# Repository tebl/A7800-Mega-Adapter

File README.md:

# Atari 7800 Mega Adapter
Let's face it, the controllers that came with the Atari 7800 are truly painful to use... unfortunately, both of the variants for the system suffer from the same problem (just for different reasons)! This may go a long way to explain why I've spent somewhere around an hour total playing on the system despite owning it for a few years, so I thought it was about time I did something about it. The easiest option is to just use a single-button joystick, but then I'd lose out on the features the second button provides so I decided to just use a different controller instead; the Sega Mega Drive / Genesis controller.

I based this project on the FAQ over at AtariAge.com, so if the design looks like something you've seen before then that's probably the reason why. I've built it up and tested it on my Atari 7800 PAL system, seems to work pretty good with the wired 3-button controller (don't have a 6-button variant to test out with). Unfortunately it doesn't seem to work with the new wireless 8bitdo controllers, but at least I finally get to test out some of the games without my hands aching and turning intolerable after 5-minutes of game time.

If you want an alternative to using a Sega Mega Drive controller, I've also created an [adapter](https://github.com/tebl/C64-JoyKEY/tree/main/adapters/Atari%207800) so that my [C64 JoyKEY](https://github.com/tebl/C64-JoyKEY)-controller can be used with the Atari 7800 system.

## Building the adapter
Mark Fixes Stuff on Youtube did a segment called [Making a Sega Megadrive Controller Adapter for Atari 7800! Full Build & Games Testing!](https://www.youtube.com/watch?v=7EVtcfSCWJM) that shows every part of assembling this adapter, particularly useful for those of us that are not used to soldering together new equipment from a bucket of parts. Keep reading from at more text-oriented description of the assembly process.

One thing to note, the main PCB of the Atari 7800 isn't actually mounted flat so the controller ports are actually angled quite a bit downwards! This means that the female DSUB-9 port that goes into the Atari 7800 will have to be soldered in place at an agle, preferably as far as you can take it and still be able to solder the pins into place.

As can also be seen in the picture above, the metal shroud that comes mounted on the female DSUB-9 has been removed after soldering it into place. The male connectors on the Atari 7800 console is made out of plastic and not metal, so it no longer serves a purpose - the plastic on these have also grown brittle over the years, so reducing the strain on it will hopefully also keep it from splitting).

# Schematic
The supplied KiCad files should be sufficient as both a schematic and as a  starting point for ordering PCBs (basically you could just zip the contents of the export folder and upload that on a fabrication site), the schematic is also available in [PDF-format](https://github.com/tebl/A7800-Mega-Adapter/blob/master/export/A7800%20Mega%20Adapter.pdf) and this is what you'll need to print and work your way through this things don't work as expected after assembly.

# BOM
Most parts should be easy to get a hold of from your favourite local electronic component shop, but given that I don't have access to such shops where I live so everything was based on whatever I could get cheapest from eBay/AliExpress (free shipping, plan on waiting 3-4 weeks for delivery though).

| Reference    | Item                                  | Count | Order |
| ------------ | ------------------------------------- | ----- | ----- |
| PCB          | Fabricate using Gerber files          |     1 | [PCBway](https://www.pcbway.com/project/shareproject/Atari_7800_Mega_Drive_adapter.html) |
| J1           | Female DB9 right-angle connector      |     1 |       |
| J2           | Male DB9 right-angle connector        |     1 |       |
| Q1,Q2        | 2N3906 TO-92 transistor               |     2 |       |
| R1,R3        | 620 ohm resistor                      |     2 |       |
| R2,R4        | 1k ohm resistor                       |     2 |       |

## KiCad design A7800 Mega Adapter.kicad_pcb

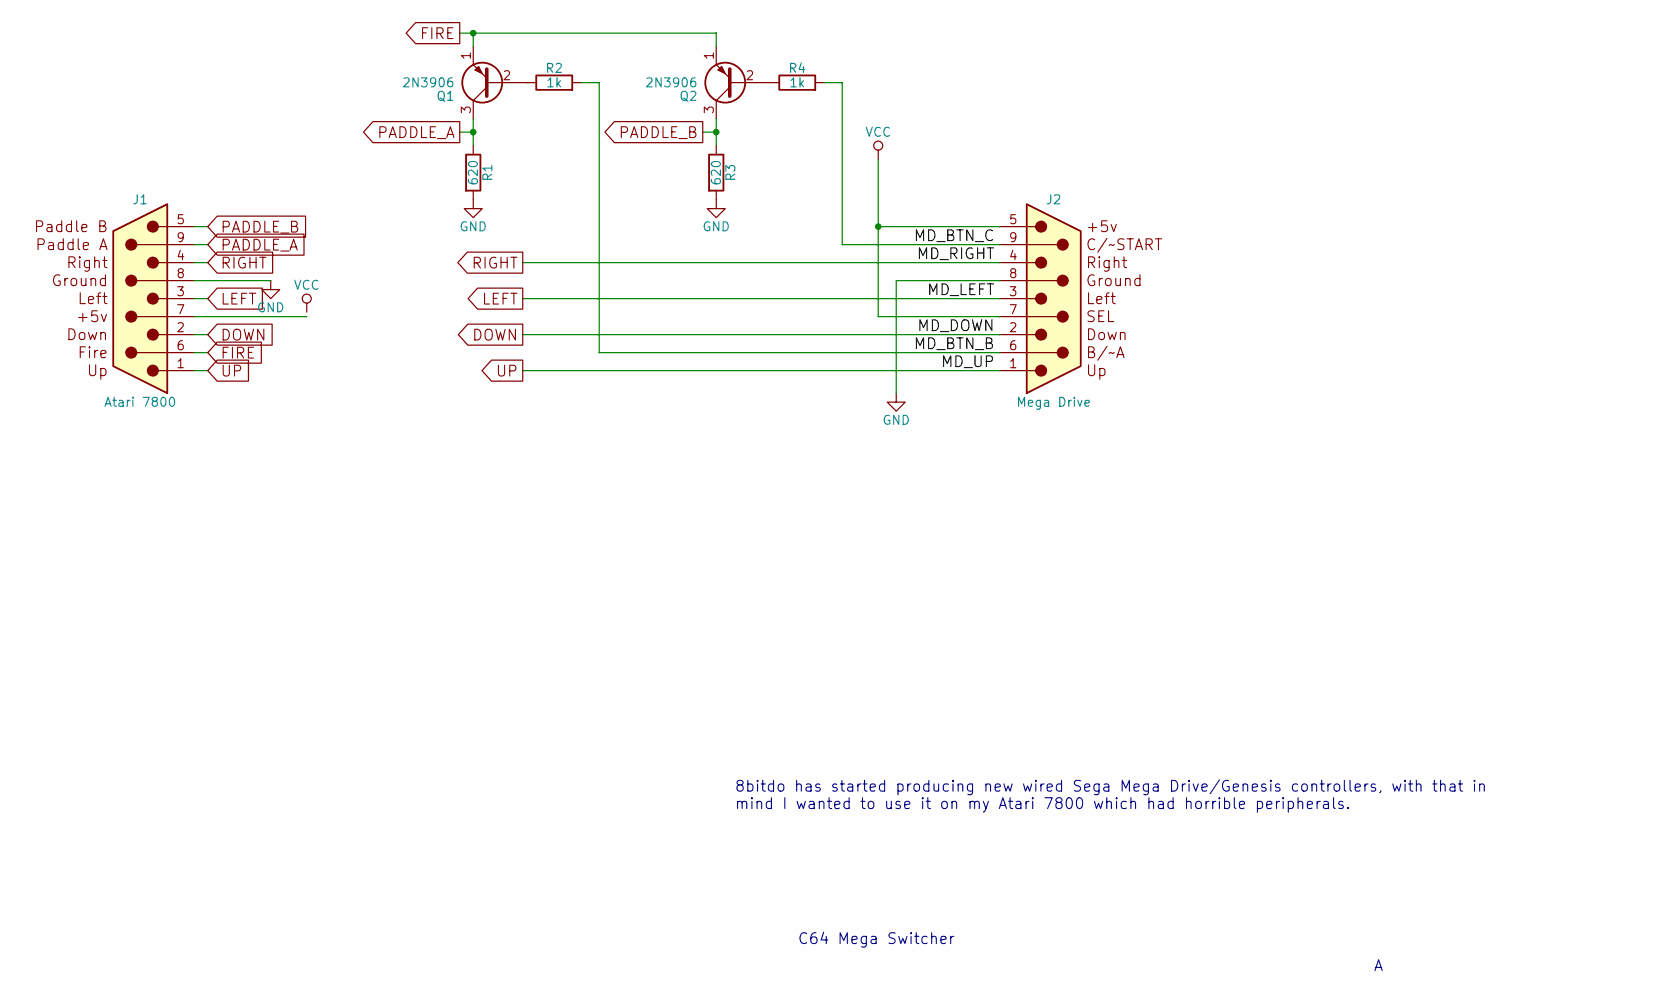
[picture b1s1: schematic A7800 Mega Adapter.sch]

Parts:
J1: Atari 7800; DSUB-9_Female_Horizontal_P2.77x2.84mm_EdgePinOffset7.70mm_H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
J2: Mega Drive; DSUB-9_Male_Horizontal_P2.77x2.84mm_EdgePinOffset7.70mm_Hou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
Q1, Q2: 2N3906; TO-92_Inline_Wide
R1, R3: 620; R_Axial_DIN0207_L6.3mm_D2.5mm_P10.16mm_Horizontal
R2, R4: 1k; R_Axial_DIN0207_L6.3mm_D2.5mm_P10.16mm_Horizontal

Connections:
/MD_BTN_B: J2.6, R2.2
/MD_BTN_C: J2.9, R4.2
DOWN: J1.2, J2.2
FIRE: J1.6, Q1.1 (E), Q2.1 (E)
GND: J1.8 (GND), J2.8 (GND), R1.2, R3.2
LEFT: J1.3, J2.3
unnamed: Q1.2 (B), R2.1
unnamed: Q2.2 (B), R4.1
PADDLE_A: J1.9, Q1.3 (C), R1.1
PADDLE_B: J1.5, Q2.3 (C), R3.1
RIGHT: J1.4, J2.4
UP: J1.1, J2.1
VCC: J2.5 (VCC), J2.7

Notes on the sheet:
C64 Mega Switcher
8bitdo has started producing new wired Sega Mega Drive/Genesis controllers, with that in mind I wanted to use it on my Atari 7800 which had horrible peripherals.

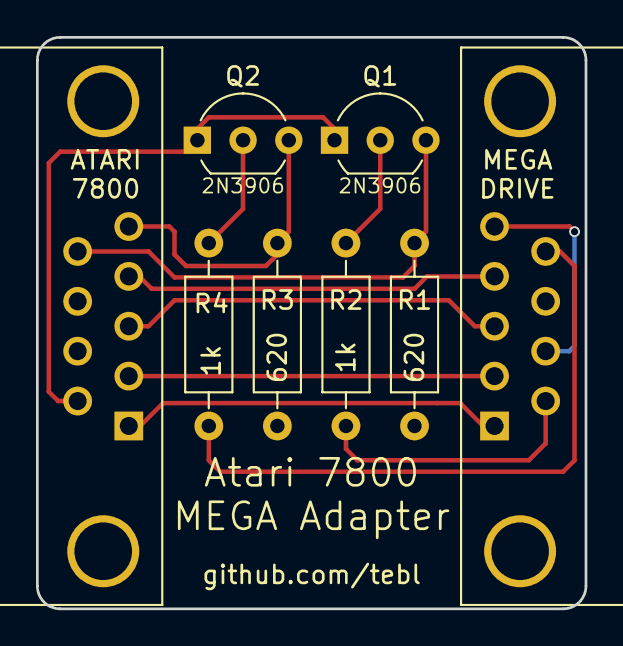
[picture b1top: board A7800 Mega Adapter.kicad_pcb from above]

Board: 2 copper layers, 30.5 x 31.8 mm, 8 parts (0 on the bottom side), 13 nets.

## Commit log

2019-12-17 Fixed VCC wire
2020-01-27 Added picture
2021-03-11 Added images
2021-03-11 Changed build description

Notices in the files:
A7800 Mega Adapter.kicad_pcb:
Licensed under
CERN OHL v.1.2
